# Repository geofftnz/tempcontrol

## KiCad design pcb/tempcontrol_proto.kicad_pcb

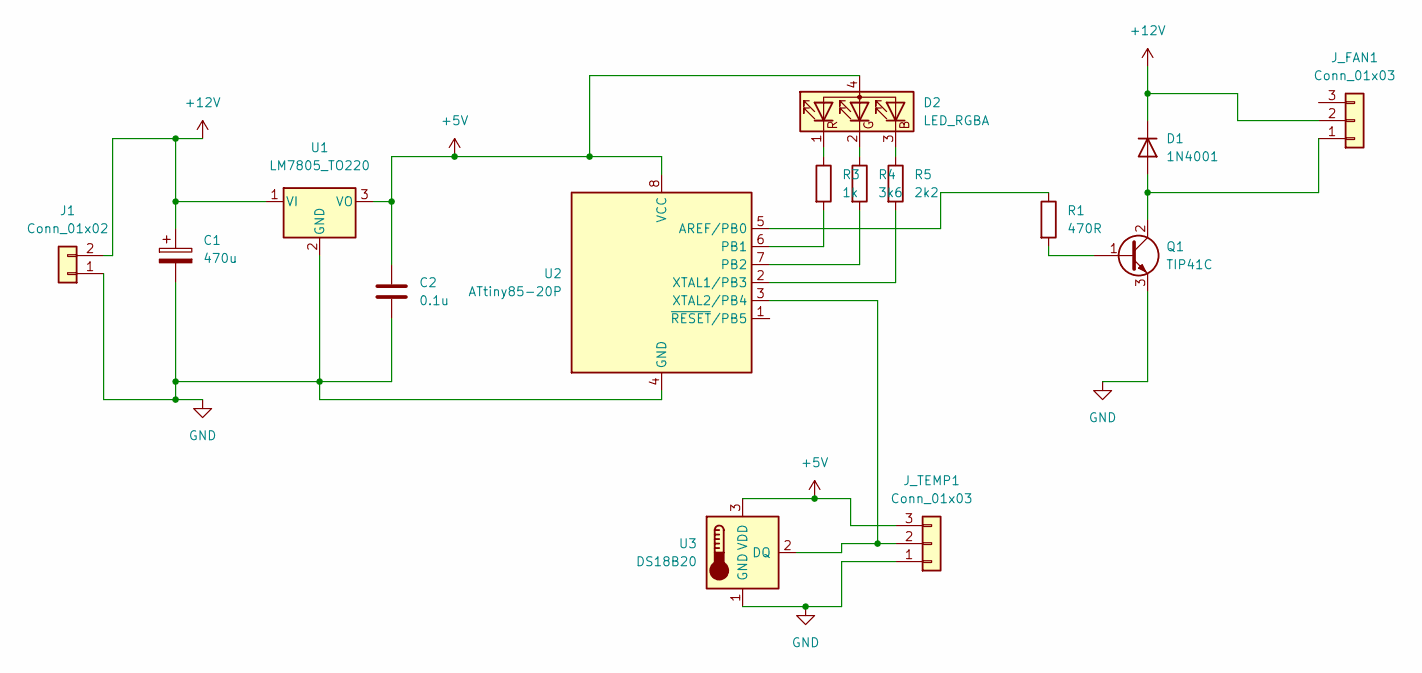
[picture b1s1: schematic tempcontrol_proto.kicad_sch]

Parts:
C1: 470u; CP_Radial_D8.0mm_P2.50mm
C2: 0.1u; C_Disc_D5.1mm_W3.2mm_P5.00mm
D1: 1N4001; D_DO-41_SOD81_P5.08mm_Vertical_AnodeUp
D2: LED_RGBA; LED_D5.0mm-4_RGB_Wide_Pins
J1: Conn_01x02; Molex_KK-254_AE-6410-02A_1x02_P2.54mm_Vertical
J_FAN1: Conn_01x03; Molex_KK-254_AE-6410-03A_1x03_P2.54mm_Vertical
J_TEMP1: Conn_01x03; Molex_KK-254_AE-6410-03A_1x03_P2.54mm_Vertical
Q1: TIP41C; TO-220-3_Vertical
R1: 470R; R_Axial_DIN0204_L3.6mm_D1.6mm_P2.54mm_Vertical
R3: 1k; R_Axial_DIN0204_L3.6mm_D1.6mm_P2.54mm_Vertical
R4: 3k6; R_Axial_DIN0204_L3.6mm_D1.6mm_P2.54mm_Vertical
R5: 2k2; R_Axial_DIN0204_L3.6mm_D1.6mm_P2.54mm_Vertical
U1: LM7805_TO220; TO-220-3_Vertical
U2: ATtiny85-20P; DIP-8_W7.62mm
U3: DS18B20; TO-92_Inline

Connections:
+5V: C2.1, D2.4 (A), J_TEMP1.3, U1.3 (VO), U2.8 (VCC), U3.3 (VDD)
+12V: C1.1, D1.1 (K), J1.2, J_FAN1.2, U1.1 (VI)
GND: C1.2, C2.2, J1.1, J_TEMP1.1, Q1.3 (E), U1.2 (GND), U2.4 (GND), U3.1 (GND)
unnamed: D1.2 (A), J_FAN1.1, Q1.2 (C)
unnamed: D2.1 (RK), R3.1
unnamed: D2.2 (GK), R4.1
unnamed: D2.3 (BK), R5.1
unnamed: J_TEMP1.2, U2.3 (XTAL2/PB4), U3.2 (DQ)
unnamed: Q1.1 (B), R1.2
unnamed: R1.1, U2.5 (AREF/PB0)
unnamed: R3.2, U2.6 (PB1)
unnamed: R4.2, U2.7 (PB2)
unnamed: R5.2, U2.2 (XTAL1/PB3)

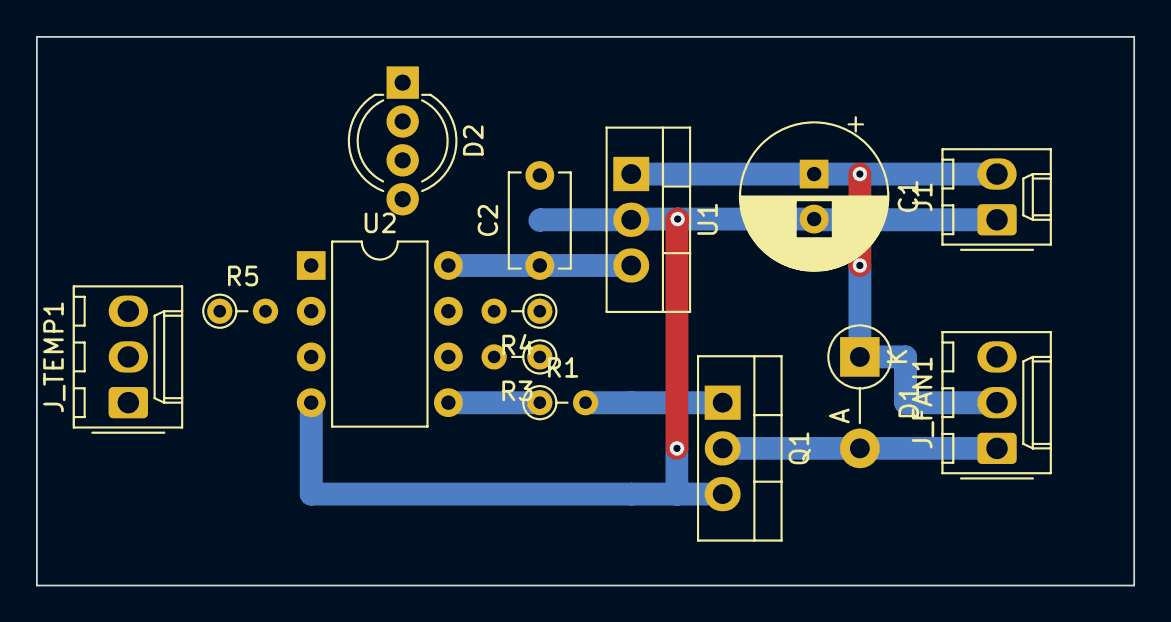
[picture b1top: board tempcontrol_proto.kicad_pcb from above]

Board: 2 copper layers, 61.0 x 30.5 mm, 14 parts (0 on the bottom side), 13 nets.

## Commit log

2022-04-29 initial
2022-04-29 high speed pwm
2022-05-01 tweaks
2022-10-23 fix LED outputs.
